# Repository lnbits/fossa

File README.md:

<a href="https://lnbits.com" target="_blank" rel="noopener noreferrer">
  <picture>
    <source media="(prefers-color-scheme: dark)" srcset="https://i.imgur.com/QE6SIrs.png">
    
  </picture>
</a>

The low-cost Bitcoin Lightning ATM built with simple parts like an ESP32 and coin/bill acceptors. It lets anyone turn fiat into Bitcoin and comes with clear instructions so hobbyists and developers can easily build their own.

Bitcoin withdrawals are now possible via LNURL, Bolt11, onchain, Liquid and lightning addresses 🔥

## Bill of Materials

Roughly available for £200-£250!

You can run the FOSSA as a coin machine, a bill acceptor, or both.

### Primary FOSSA components
| Part    | Description    | Buy (UK)    | Estimated cost |
|-------------|-------------|-------------|-------------|
| ESP32 WT32-SC01 | ESP32 touchscreen (not the PLUS). Comes with USB-C cable. | Ebay or [AliExpress](https://www.aliexpress.com/item/1005003191471709.html) | **£45** |
| NV10USB+ bill acceptor | Optional: accepts banknotes (set to GBP + SIO). | [Ebay (second hand)](https://www.ebay.co.uk/itm/263398460026) | **£70-£150** |
| DG600F(S) Multi Coin Acceptor | Optional: accepts coins (S = stainless steel front). | [AliExpress](https://www.aliexpress.com/w/wholesale-DG600F(S)-Multi-Coin-Acceptor.html?spm=a2g0o.home.search.0) or eBay | **£30** |
| Screw terminal block | Connect wires, no soldering. | [Amazon (UK)](https://www.amazon.co.uk/gp/product/B08LNWMMHQ) | **£1** |
| 12v power supply | 12V supply (battery also works). | [Amazon (UK)](https://www.amazon.co.uk/gp/product/B09MTBTXDJ/) | **£8** |
| 12v to 5v step down converter with USB | Converts 12V to stable 5V/3A. | [Amazon (UK)](https://www.amazon.co.uk/gp/product/B07QQ587K3) | **£5** |
| Male-to-female GPIO jumpers | Plug-and-play wires. | [Amazon (UK)](https://www.amazon.co.uk/gp/product/B09MJZDXBB) | **£5** |
| Aluminum "medicine box" | Optional: cheap case option. | Amazon (UK) | **£30** |
| Amazon Basic Home Safe | Optional: stronger case option. | Amazon (UK) | **£70** |
| 58mm 701 USB Thermal Receipt Printer | Optional: prints receipts (doesn’t fit enclosure yet). | [Ebay (UK)](https://www.ebay.co.uk/itm/293668439213) | **£25** |

### 3D printed enclosure fixtures & fittings

For the 3D-printed version, you will need:

| Part    | Description    | Buy (UK)    |
|-------------|-------------|-------------|
| M4 x 16mm pan head security torx bolts | Hold front facia to back box (14–55mm length works). | [Amazon (UK)](https://www.amazon.co.uk/gp/product/B0BTTRPBQV/) |
| Tamper-proof torx wrench (T20) | Tighten facia Torx bolts. | [Amazon (UK)](https://www.amazon.co.uk/gp/product/B0D53LNNRW) |
| Brass insert nuts, M4 x 6mm | Heat-set nuts for 3D prints (use soldering iron). | [Amazon (UK)](https://www.amazon.co.uk/gp/product/B09MCVW4GQ/) |
| M4 x 30mm carriage bolts | Replace coin acceptor bolts for facia thickness. | [eBay (UK)](https://www.ebay.co.uk/itm/386550912089?var=653926055961) |
| 5.5mm x 2.1mm DC power jack socket | Mounts 12V adaptor plug on box exterior. | [Amazon (UK)](https://www.amazon.co.uk/dp/B01N3679B8) |
| 2.2mm quick disconnect spade connector | Crimp cable to connect power jack socket. | |
| 16mm cabinet tubular lock | Lock for the door. | [Amazon (UK)](https://www.amazon.co.uk/Litensh-Tubular-Cylinder-Cupboard-Letterbox/dp/B09SHWXWXC/) |
| Rubber feet (D30x22xH15) | Optional: add feet for table mounting (M5 bolt or adhesive). | [Amazon (UK)](https://www.amazon.co.uk/dp/B0CQ23M5Z5) |
| M5 x 16mm hex socket bolts | Optional: secure rubber feet. | [Amazon (UK)](https://www.amazon.co.uk/16mm-Socket-Button-Head-Screws/dp/B09BG8XNM7) |
| M5 nylon nuts | Optional: secure rubber feet. | [Amazon (UK)](https://www.amazon.co.uk/Bolt-Base-Stainless-Insert-Nylock) |
| Adhesive security plate + cable | Optional: secure ATM when desk mounted. | [Amazon (UK)](https://www.amazon.co.uk/I3C-Security-Anti-Theft-Hardware-Smartphone/dp/B07FM93JL6) |

## Software installation

### Using the web-installer

With Chromium based browser visit https://fossa.lnbits.com

### Running locally

Optional: If using hardcoded values, edit `hardcoded_user_config.h`

```bash
cp fossa/hardcoded_user_config.h.example fossa/hardcoded_user_config.h
```

Fetch and install everything needed (build), then push binary to esp32 (debug):

```bash
sh chmod +x build.sh
sh ./build.sh
sh chmod +x debug.sh
sh ./debug.sh /dev/ttyUSB0
```

## Hardware Build
### Step 1: Hardware Setup

[https://www.youtube.com/watch?v=vbyYb9Yiu_k](https://www.youtube.com/watch?v=vbyYb9Yiu_k)

This method requires no soldering. We do this by using GPIO jumpers and terminal blocks. First, split a terminal block into a block of 3 (our LIVE terminal) and a block of 4 (our GROUND terminal).

The wiring reference is as follows:

**To connect the bill acceptor**:

1. Connect the Rx (GPIO 32) and Tx (GPIO 33), pins 29 and 31, on the WT32-SC01 board to pins 1 and 5, respectively, on the bill acceptor.
2. Using a GPIO jumper, connect the live wire (pin 15) to the first LIVE terminal block at an available terminal.
3. Using a GPIO jumper, connect the ground wire (pin 16) to a second GROUND terminal block of block at an available terminal.
4. Connect the positive wire (red) of the 12V to 5V power converter and connect it to the LIVE terminal block at an available terminal.
5. Connect the negative wire (black) of the 12V to 5V power converter and connect it to the GROUND terminal block at an available terminal.
6. Connect the ground pin (e.g. pin 5) of the WT32-SC01 and connect it to the 2nd terminal of the GROUND terminal block at an available terminal.

| NV10USB+ Pin | WT32-SC01 Pin No. (Not GPIO No.) | Power Supply   |
|----------|-----------|----------------|
| 1 (Tx)  | 31         | N/A |
| 5 (Rx)  | 29         | N/A |
| 15 (12V DC+) | N/A | 12V DC+ |
| 16 (GND) | 5         | GND            |

> The bill acceptor needs to be programmed to your currency and set to `SIO` mode. Usually, you can buy them preconfigured. If you have to program, buy <a href="https://www.innovative-technology.com/shop/cables/nv9-nv10-usb-host-cable-detail">this wire</a> and download the Validator Manager software <a href="https://www.dropbox.com/sh/2mle0czl2j2w7yq/AABie6AJQTq-tXmBv1TUhBUGa?dl=0">here</a> or <a href="http://www.innovative-technology.com/support/secure-download">here</a> (sadly only runs on windows, so use a friends machine). Details on programming can be found <a href="https://github.com/arcbtc/fossa/blob/main/NV10Manual_2.PDF.pdf">here</a>. It's relatively straightforward to program the acceptor: plug in the USB host cable, turn it on by holding the config button for 2 seconds, and open the Validator Manager software. If you prefer to build your own programming cable, see page 42 of the <a href="NV10 operations manual.pdf">NV10 USB Operations Manual</a>, which gives a wiring diagram for the NV10 USB host cable. You can ignore all the hardware requirements for programming in the guide; you just need the host cable! Don't try using the programming cards in the guide; that's an old system these machines no longer support - "Many Bothans died to bring us this information"!

**To connect the coin acceptor**:

> NB You can usually order the coin acceptor pre-programmed to your currencies. Otherwise, you will need to train the acceptor using <a href="https://www.youtube.com/watch?v=Dyun1xjKqc4">this guide</a>.

1. Set the 3rd dip switch to high (this sends integers to the WT32-SC01 rather than pulses).
2. Using a GPIO jumper, connect the interrupt pin (pin 5) on the coin accepter to the 5V pin (pin 2) on the WT32-SC01.
3. Using a GPIO jumper, connect the serial out (pin 2) on the coin accepter to pin 4 on the  WT32-SC01.
4. Using a GPIO jumper, connect the live pin (pin 1) to the LIVE terminal block at an available terminal.
5. Using a GPIO jumper, connect the GND pin (pin 3) on the coin accepter to the GROUND terminal block at an available terminal.

| DG600F(S) Pin | WT32-SC01 Pin No. (Not GPIO No.) | Power Supply
| ------------- | ------------- | ------------- |
| 5 | 2 | N/A |
| 4 | N/A | N/A |
| 3 (GND) | N/A | GROUND
| 2 (serial out) | 4 | N/A
| 1 (12V) | N/A | LIVE

**To connect the 12V power supply**:

1. Connect a GPIO jumper to the live connection (+) on the 12V power supply terminal block adapter to the LIVE terminal block at an available terminal.
2. Connect a GPIO jumper to the ground connection (-) on the 12V power supply terminal block adapter to the GROUND terminal block at an available terminal.

**To complete the terminal blocks**:

1. Connect each terminal in the LIVE terminal block so they all receive power by looping over wires from terminals 1 to 2 and 1 to 3.
2. Connect each terminal in the GROUND terminal block so they all receive power by looping over wires from terminals 1 to 2, 1 to 3 and 1 to 4.

**To connect to power**:

1. Plug in the WT32-SC01 to the USB connector of the 12V to 5V power converter.
2. Plug in the connection terminal of the 12V power supply and connect to mains power.

You should hear the bill acceptor and coin acceptors turn on.

### Step 2: Configure LNBits

To configure your LNBits instance (requires v1.3.0+) to pull funds from:

1. Login to your instance of LNBits.
2. Create a wallet.
3. Go to `Manage Extensions`, find `FOSSA`, and install/enable it.
4. Open the `FOSSA` extension, click `New FOSSA`, give it the title of `ATM`, and choose the appropriate wallet for the ATM. Select the correct currency (e.g., `GBP`), the wallet to use, and a percentage for the commission.
5. Copy the link it gives you.

### Step 3: Programming the WT32-SC01

The ATM is configured in two parts: the ATM and LNBits running on a separate node.

To set up your Arduino IDE:

1. If you have not already done so, install the Arduino IDE from [https://www.arduino.cc/en/Main/Software](https://www.arduino.cc/en/Main/Software).
2. Install the ESP32 libraries. You can do this by copying the stable release version link, currently `https://espressif.github.io/arduino-esp32/package_esp32_index.json` and putting in the `File` > `Preferences...` > `Additional Board Manager URLs` (see: [https://docs.espressif.com/projects/arduino-esp32/en/latest/installing.html](https://docs.espressif.com/projects/arduino-esp32/en/latest/installing.html))
3. Install the boards by going to `Tools` > `Board` > `Board Manager...`, searching for ESP32, choose 2.0.17, and click Install.
4. Copy the libraries from this project <a href="/libraries">libraries</a> folder to your `"/Arduino/libraries"` folder (usually in OS `"Home"` directory)
5. Clone the repo and open accessPointFOSSA.
6. Select the relevant port and ESP32 dev module.
7. Go to `Sketch` > `Upload`.
8. Once uploaded, the access portal will launch when you press the screen on the WT32-SC01 device.

To configure the ATM:

1. Connect the access portal wi-fi (`Device-fa7ce5a4`, for example).
2. Open the access portal.
2. Enter a new password.
3. Enter the coin denominations (if you are using a coin acceptor, separated by a comma)
4. Enter the maximum withdrawal amount in fiat (e.g. `30` for 30 GBP).
5. Enter a percentage charge for the service (e.g. `10` for 10%, which should be the same value you entered into LNBits).
6. Click `Save`.
7. unplug and plug the WT32-SC01 back in once saved. You should see the `Fiat for Sats` screen.

### Step 4: Enclosure

> It should be pointed out that this ATM is designed to be attended to (such as on a shop counter) rather than something that can be left unattended and mounted to a wall.

#### Option A: 3D printed enclosure

If you want to want to print your own enclosure, we recommend these settings:

1. Print the Facia
    - STL: [FOSSA ATM Facia](https://github.com/lnbits/fossa/blob/main/3DPrints/FOSSA%20ATM%20Facia.stl)
    - Material: PETG
    - Layer: 0.2mm
    - Infill: 10-100% (recommend 20%+)
    - Supports: Yes
    - Notes: To set the Bitcoin logo with a different color, set a color change at layer 114 (13.20mm). In PrucaSlicer, you can "paint" out all the screw holes as they do not need supports. I would also recommend setting a thicker layer parameter, in PrucaSlicer, you can do this by settings `Printer Settings` > `Layers and perimeters` > `Perimeters` to `4`)
3. Print the backbox
    - STL: [FOSSA ATM Backbox](https://github.com/lnbits/fossa/blob/main/3DPrints/FOSSA%20ATM%20Back%20Box.stl)
    - Material: PETG
    - Layer: 0.2mm
    - Infill: 10-100% (recommend 20%+)
    - Supports: Yes
    - Notes: In PrusaSlicer you can set `Print Settings` > `Support material` > `First layer expansion` to `1 mm`, `XY separation between an object and its support` to `80%` and `Overhang threshold` to `1 mm`, or, you can "paint" out all but the door as the model has been designed for minimal supports
4. Print the accessories
    - STL: [FOSSA ATM WT-32-SC01 Backplate](https://github.com/lnbits/fossa/blob/main/3DPrints/FOSSA%20ATM%20WT-32-SC01%20Backplate.stl), [FOSSA ATM Coin Slot Cover](https://github.com/lnbits/fossa/blob/main/3DPrints/FOSSA%20ATM%20Coin%20Slot%20Cover.stl), [FOSSA ATM 4mm Lock Lever Shim](https://github.com/lnbits/fossa/blob/main/3DPrints/FOSSA%20ATM%204mm%20Lock%20Lever%20Shim.stl), [FOSSA ATM Door](https://github.com/lnbits/fossa/blob/main/3DPrints/FOSSA%20ATM%204mm%20Door.stl), [FOSSA ATM Backbox Note Holder](https://github.com/lnbits/fossa/blob/main/3DPrints/FOSSA%20ATM%20Backbox%20Note%20Holder.stl)
    - Material: PETG
    - Layer: 0.2mm
    - Infill: 10-100% (recommend 20%+)
    - Supports: No
5. Use a soldering iron to melt the brass female embedded insert nuts into the six holes for the facia (see picture 1 below)
6. OPTIONAL: If using the coin acceptor, replace the coach bolts with longer bolts (M4 x 30mm carriage/coach bolts) to account for the thickness of the facia.
7. Mount the bill acceptor so it is "smiling" (see picture 2) with the supplied mounting bracket and screws as pictured (see picture 3). You can remove the bill input feed from the main part of the unit and then re-attach it.
8. Mount the screen to the WT-32-SC01 Backplate.
9. Mount the backplate to the Facia with the M4 (4mm x 8mm Inc Head) hex socket countersunk screws.
10. Mount the backbox note holder to the backbox with the M4 (4mm x 8mm Inc Head) hex socket countersunk screws.
11. Mount the 5.5mm x 2.1mm DC Power Jack Socket Female Panel Mount Connector in the hole in the back left of the backbox (this directs the notes to the bottom of the box.
12. Connect wires from the connection terminal to the 2.2mm Quick Disconnect Female Spade Connector and plug into the inside of the 5.5mm x 2.1mm DC Power Jack Socket Female Panel Mount Connector.
13. OPTIONAL: Mount the Rubber feet (D30x22xH15) using the M5 x 16mm hex socket bolts and M5 nylon nuts (be careful not to over-tighten).
14. Using the Tamper-proof torx wrench (T20), use the screw in the M4 x 16mm pan head security torx tamper-resistant bolts to secure the facia to the backbox.
15. Plug the power supply in.

#### Option B: Mount in a box

Use the templates provided <a href="cuttingTemplate.pdf">here</a>, print out at 100% on standard UK A4, and check the dimensions are correct after printing. It's helpful if the bill acceptor and coin mech pins are accessible.

* For the `Aluminium Storage Box` solution, holes can be cut with a sharp knife (clearly not secure - but acceptable for somewhere you can keep an eye on the ATM or for demos).

* For the `Home Safe` solution, holes can be cut with an angle grinder and a very thin cutter. (If you have not used an angle grinder before, don't be scared; they're cheap, easy enough to use, and very useful. Take your time and wear safety equipment.)

> We use CT1 sealant/adhesive (or similar) for mounting the screen, although the screen has screw points, which should prob be used for added security.

## Get in touch

And there you have it. Have fun, and tag us on Twitter / Nostr with all your cool setups!

> <i>Join our <a href="https://t.me/makerbits">telegram support/chat</a>.</i>

## Powered by LNbits

[LNbits](https://lnbits.com) is a free and open-source lightning accounts system.

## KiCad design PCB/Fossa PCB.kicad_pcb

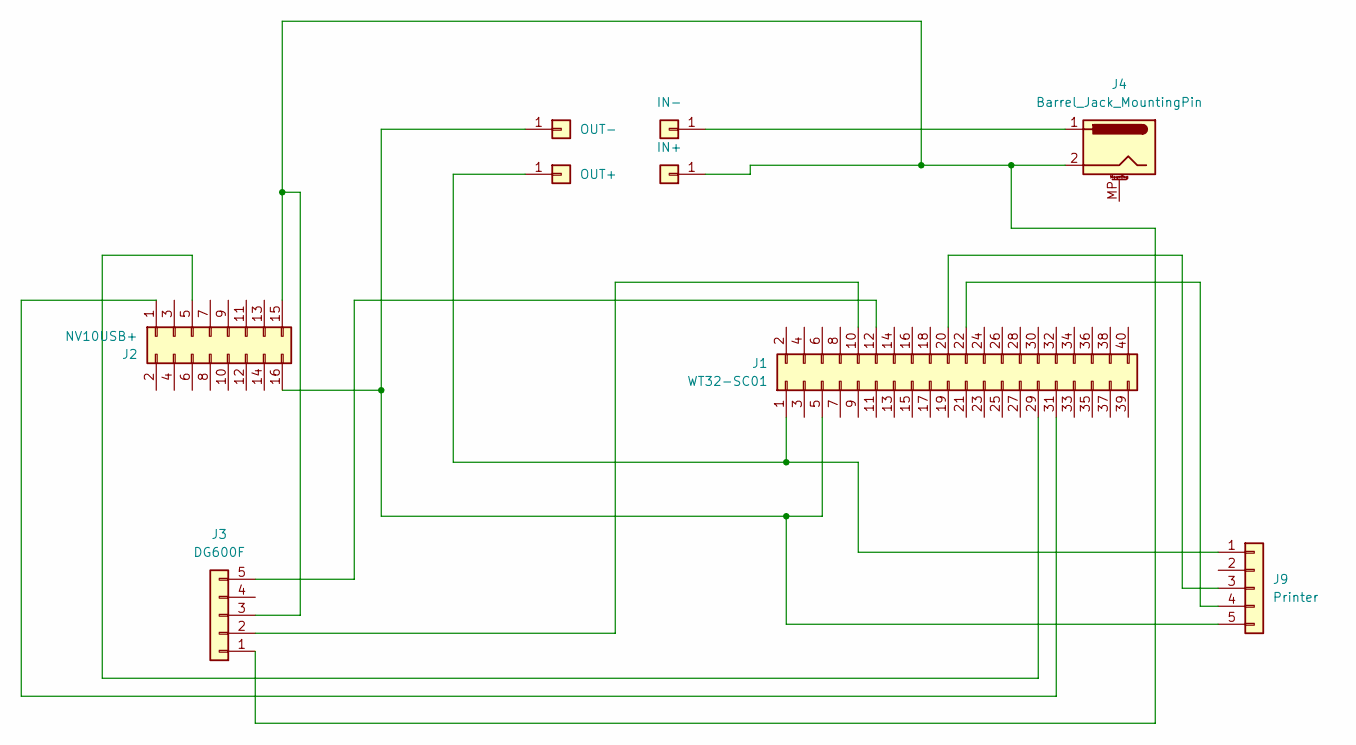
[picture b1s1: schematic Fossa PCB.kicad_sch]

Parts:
J1: WT32-SC01; PinHeader_2x20_P2.00mm_Vertical
J2: NV10USB+; PinHeader_2x08_P2.54mm_Vertical
J3: DG600F; PinHeader_1x05_P2.54mm_Vertical
J4: Barrel_Jack_MountingPin; BarrelJack_CUI_PJ-063AH_Horizontal
J5: IN+; PinHeader_1x01_P2.54mm_Vertical
J6: IN-; PinHeader_1x01_P2.54mm_Vertical
J7: OUT+; PinHeader_1x01_P2.54mm_Vertical
J8: OUT-; PinHeader_1x01_P2.54mm_Vertical
J9: Printer; PinHeader_1x05_P2.54mm_Vertical

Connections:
unnamed: J1.1, J7.1, J9.1
unnamed: J1.5, J2.16, J8.1, J9.5
unnamed: J1.10, J3.2
unnamed: J1.12, J3.5
unnamed: J1.20, J9.3
unnamed: J1.22, J9.4
unnamed: J1.29, J2.5
unnamed: J1.31, J2.1
unnamed: J2.15, J3.1, J3.3, J4.2, J5.1
unnamed: J4.1, J6.1

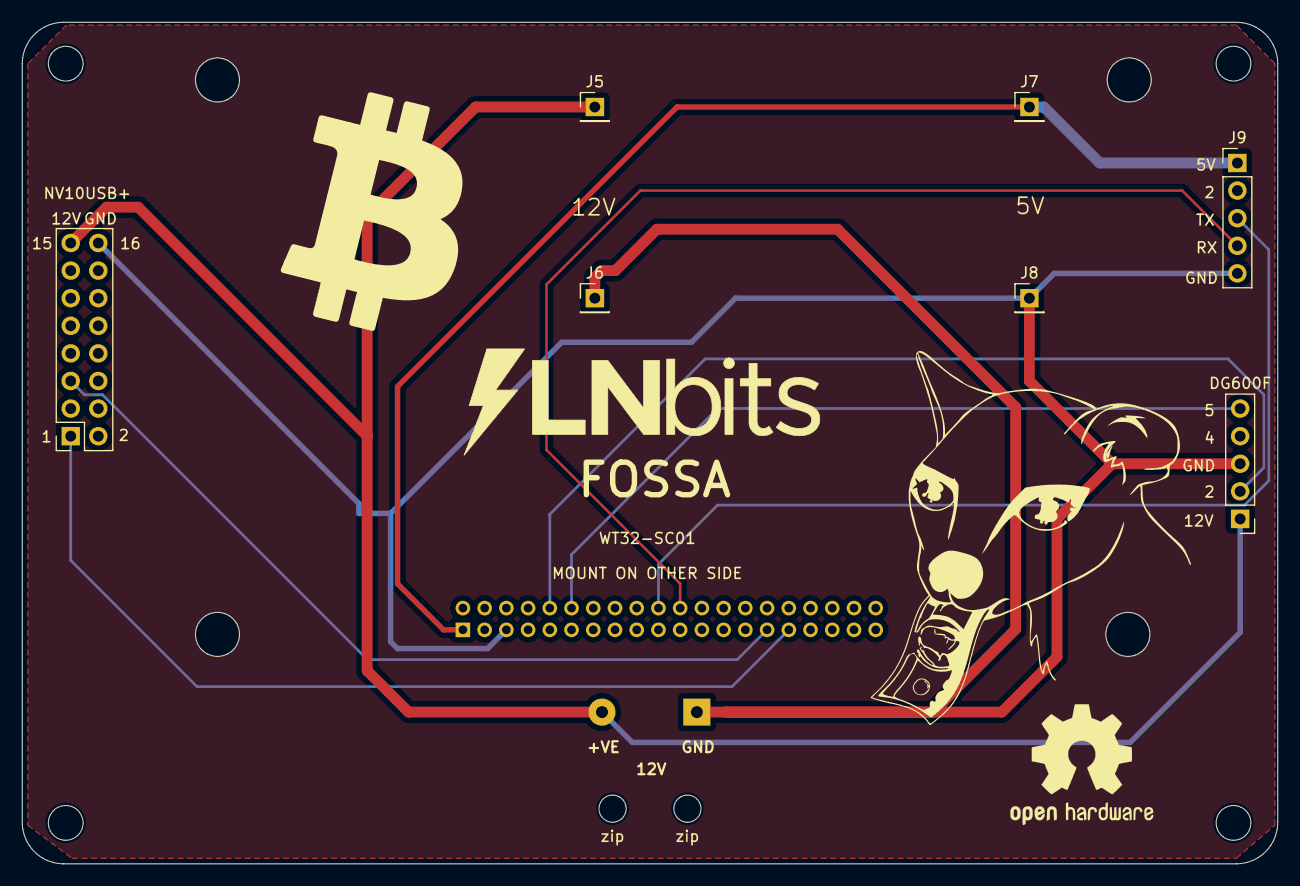
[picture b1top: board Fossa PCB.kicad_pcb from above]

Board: 2 copper layers, 115.6 x 77.5 mm, 11 parts (1 on the bottom side), 10 nets.

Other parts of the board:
zip: zip; MountingHole_2.5mm
zip#2: zip; MountingHole_2.5mm

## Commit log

2023-01-18 Fix bug where accepted coins wasnt being loaded from user configured settings
2023-01-19 Added Leigh's cutting template to repo
2023-01-19 Fix bug where accepted notes wasnt being loaded from user configured settings
2023-01-19 Added WT32-SC01 case
2023-01-19 Added NV10 manual with host cable wiring diagram for DIY host programming cable build
2023-01-19 Renamed NV10 operations manual and user manual files to make repo easier to navigate
2023-01-23 Added WT32SC01 to Templates
    Added WT32SC01 to Templates
2024-07-01 Work on printer
2024-07-02 Working receipt printer!
2024-07-02 NOw all connected devices work!
2024-07-02 Switched printer to use software serial and it works!
2024-07-02 Added esp software serial and thermal printer libraries
2024-07-03 bug fix on total printed on receipt
2024-07-03 Added a few more quotes
2024-07-03 Added PCB
2024-07-03 Update receipt printing message position
2024-07-03 Updated screen layout code and credited Leigh for QR printing code in README
2024-07-08 Added Wiring diagram and organised docs a bit
2024-07-08 Removed old stls and added new PCB enclosure
2024-07-08 Updated bill acceptor wiring diagram
2024-07-08 Update cutting template file and desc
2024-07-08 Move nv10 wiring table into markdown
2024-07-08 Clarify pin number not GPIO number on nv10 table in readme
2024-07-15 Corrected 12v and GND labels on board
2024-07-21 Draft FOSSA Facia & Slot cover
    More coming soon. Will be amending for clearance with the screen.
2024-07-22 Prototype back box
    This is a prototype backbox for the FOSSA ATM.
2024-07-22 Removed top-left pillar
    The top left pillar would clash with the top left bolt pruding out of the back of the coin acceptor so have removed.
2024-07-23 Screen mount test added
    This uses the same sketch.
2024-07-23 Updated the ATM Facia
    - Additional mounting holes at the back for an optional solenoid lock
    - Additional mounting holes for a 1591L proto board or 2 Channel Relay Breakout for the solenoid lock
    - Added more clearance for the WT32-SC01
    - Additional cooling vent for the WT32-SC01
    - Added more clearance to the 16-pin connectors on the WT32-SC01
    - Small adjustments made to the rounding and dimensions of the cash and coin acceptors
2024-07-24 Removed support that clashes with cash acceptor
    The triangular brace on the side clashed slightly with the cash acceptor so have removed it.
2024-07-24 Reference model of the WT32-SC01 ESP32
2024-07-24 Update README.md
    Added bill of materials with links and details on 3D printing.
2024-07-25 Update README.md
    Added additional Arduino and LNBits instructions.
2024-07-25 Update README.md
    Typo.
2024-07-25 Update README.md
    Added pictures and more details to the 3D print.
2024-07-25 Update README.md
    Added into graphic.
2024-07-25 Update README.md
    Added introductory paragraph. Good for search engines.
2024-07-25 Update README.md
    Reduced image sizes.
2024-07-25 Update README.md
    Minor amendments and formatting improvements.
2024-07-25 Update README.md
    Amended header image.
2024-07-25 Update README.md
    Minor text changes to the programming cable section to be more clear.
2024-07-25 Update README.md
    Tweaked alignment in the image.
2024-07-25 Create PSDs
2024-07-26 Door added
    This is the door. You will also need the lever shim to affix to the inside of the case.
2024-07-26 3mm and 4mm door lock lever shims
2024-07-28 Update README.md
    Miscellaneous typos corrected.
2024-07-30 Updated models
    Lots of various amendments.
2024-07-30 Update README.md
    3D print specifics.
2024-08-01 Update README.md
    Updated printer settings.
2024-08-01 Added LNBits board cover
2024-08-09 Various updates
    Updated noAccessPointSimpleFOSSA.ino
    Updated Readme.md
2024-08-09 feat: add new hardware installer
2024-08-14 bye bye bloat
2024-08-14 whoops forgot these
2024-08-14 Added if for if printer doesnt exist
2024-08-15 Minor
2024-08-16 For Ben
2024-08-16 Added fallback
2024-08-16 Added translations
2024-08-16 improved translations
2024-08-19 Added max fiat to consume
2024-09-23 Changed to relevant fields
2024-09-23 fossaizing
2024-09-23 fixup!
2024-09-23 feat: add new hardware installer (#14)
    * feat: add new hardware installer
    ---------
2024-09-23 [CHORE] update version to v0.0.0
2024-09-23 fix: versions.json
2024-09-23 fix: run static page build after release
2024-09-24 tweaks
2024-09-24 [CHORE] update version to v0.0.1
2024-09-24 tweaksss
2024-09-24 fixing coin
2024-09-24 [CHORE] update version to v0.0.2
2024-09-24 [CHORE] update version to v0.0.3
2024-09-24 fix: ben's tweaks
    tweaksss
    fixing coin
    tweaks
2024-09-24 fix: deploy always from main
2024-09-24 fixed translation bug
2024-10-05 fix: build was broken
2024-10-05 fix: build was broken (#16)
2024-10-05 [CHORE] update version to v0.1.0
2024-10-05 clear screen after error displays
2024-10-05 clear screen after error displays (#17)
2024-10-05 [CHORE] update version to v0.2.0
2024-10-05 typo
2024-10-05 Removed print error
2024-10-05 [CHORE] update version to v0.3.1
2024-10-05 stray print
2024-10-05 [CHORE] update version to v0.3.2
2024-10-10 Added tests
2024-10-10 Fixed print er and printer test file
2024-10-10 readme
2024-10-10 added initialise
2024-10-10 added an extra read to clear accidental taps
2024-10-10 [CHORE] update version to v0.3.3
2025-02-12 3D print latest
2025-03-05 Added tests
    Fixed print er and printer test file
    readme
    added initialise
    added an extra read to clear accidental taps
2025-03-05 fix: static page ci
2025-03-05 fix: static page ci (#19)
2025-03-05 Added WT32SC01 to Templates (#5)
2025-03-06 feat: add debug script
2025-03-06 feat: add debug script (#20)
2025-03-06 feat: define hardcoded and devices
2025-03-06 variables
2025-03-06 feat: define hardcoded and devices (#21)
2025-03-06 feat: add 100_config_tft.ino
    make it more obvious what and how to configure
2025-03-06 use config file with explainiation
2025-03-06 remove tft lib and add user txt config
2025-03-08 finally did it
2025-03-08 use previous config
2025-03-08 feat: tft_config.txt make tft configurable without changing the library (#22)
2025-03-09 feat: change to aes-cbc encryption
    more fixes
    move forward
    fix between
2025-03-09 revert layout
2025-06-21 Remove leftover coin-insertion debug warning
2025-06-21 added Dutch Language
2025-06-21 Update 101_translations.ino
    Added support for the Dutch Language [nl]
2025-06-21 Update config.js
    added dutch language "nl" config option to description
2025-08-19 Add Dutch Language [nl] (#28)
2025-08-19 Remove leftover coin-insertion debug warning (#26)
2025-08-19 baseurlatm
2025-08-19 use b64 encoding
2025-08-19 fixup use lnbits aes
2025-08-19 remove qr
2025-08-19 tap btn
2025-08-27 printer fix
2025-08-27 fix color swap
2025-08-27 little fix
2025-08-27 config fix
2025-08-27 namings
2025-08-27 removed unneeded defines
2025-08-27 few checks
2025-08-28 fixes
2025-08-28 ui working
2025-08-28 Whoops, thats an importnat one
2025-08-28 Another important one
2025-08-28 imports
2025-08-28 Translation fixes
2025-08-28 Doc clean
2025-08-28 Docs tweak
2025-08-28 hardcoded settings file
2025-08-28 added user config to gitignore
2025-08-28 stop tracking hardcoded_user_config.h
2025-08-28 Used gitignore for hardcoded
2025-08-28 reworded
2025-08-28 reword
2025-08-28 Yah, dis ist better
2025-08-28 Simpler example
2025-08-28 Encryption not brain dumping now from too small buffer
2025-08-28 Whoops
2025-09-12 DNI's aes, installer and tft_config updates (#29)
2025-09-15 add default config so it builds
2025-09-15 remove it from ignore
2025-09-15 add back
2025-09-15 fix: add default config so it builds (#30)
2025-09-15 chore: bump v0.3.0
2025-09-15 [CHORE] update version to v0.3.0
2025-09-15 better config logic
2025-09-15 tweak
2025-09-18 fix: lock to old installer
2025-09-18 fix: lock to old installer (#32)
2025-09-18 fix: error old installer
2025-09-18 fix: webinstaller again (#33)
2025-09-18 fix: better config logic (#31)
2025-09-18 [CHORE] update version to v0.4.0
2025-09-18 Change to arduino v2 in release action
2025-09-18 [CHORE] update version to v0.5.0
2025-09-18 [CHORE] update version to v0.6.0
2025-09-18 [CHORE] update version to v0.7.0
2025-09-18 [CHORE] update version to v1.0.0
2025-09-18 Auto stash before merge of "ormain" and "origin/main"
2025-09-18 just make it work with working build
2025-09-18 just upload working bins
2025-09-18 [CHORE] update version to v0.3.5
2025-09-18 version
2025-09-18 [CHORE] update version to v0.4.1
2025-09-18 Auto stash before merge of "jh" and "origin/main"
2025-09-18 better printer logic
2025-09-18 [CHORE] update version to v0.4.2
2025-09-19 reproducible build, fixed qr
2025-09-19 [CHORE] update version to v0.4.3
2025-11-15 Fix serial port
2025-11-15 Replaced the hardcoded screen width with a setting
2025-11-20 fix: annoying memory leak bug
2025-11-20 [CHORE] update version to v0.4.4
2025-11-20 add printer check
2025-11-20 [CHORE] update version to v0.4.5
2025-11-20 Just one version
2025-11-22 Update LNBits configuration instructions in README
2026-01-25 Changes to more pages
2026-01-25 Revise README with comprehensive ATM build guide
    Keep Expanded README with detailed instructions for building a Bitcoin ATM using FOSSA, including hardware setup, software installation, and enclosure option

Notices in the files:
README.md:
License: MIT
